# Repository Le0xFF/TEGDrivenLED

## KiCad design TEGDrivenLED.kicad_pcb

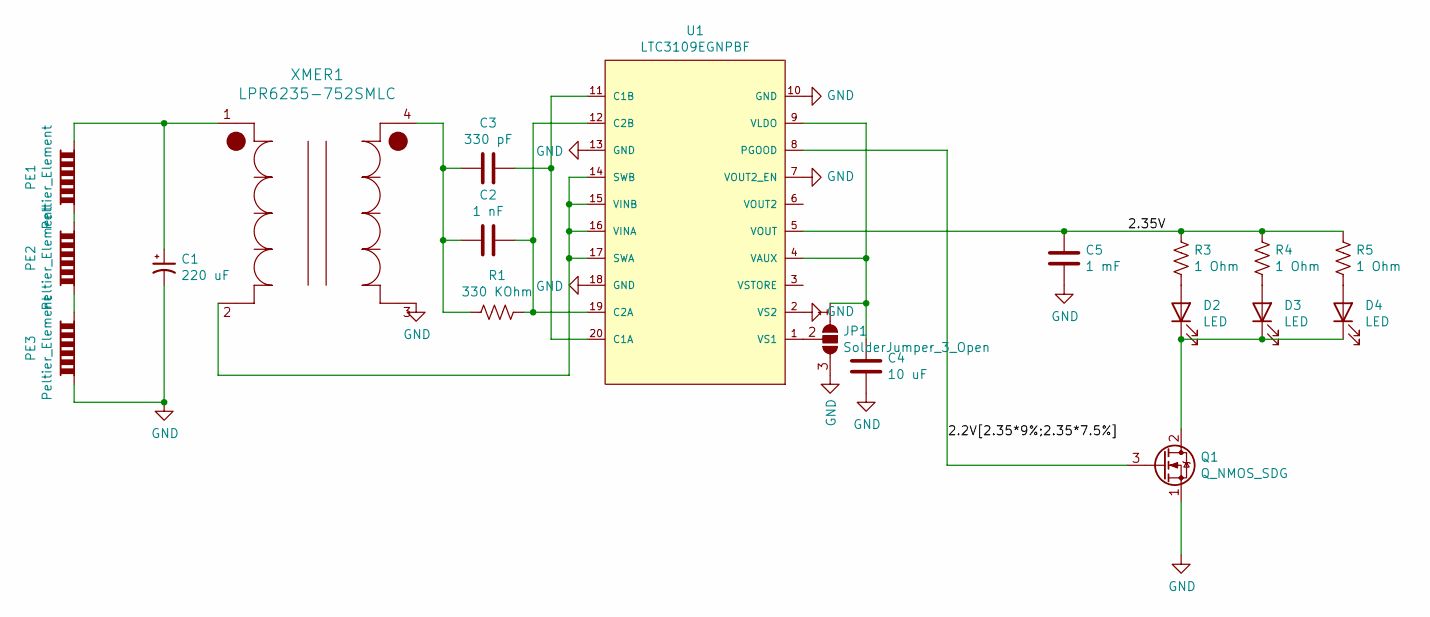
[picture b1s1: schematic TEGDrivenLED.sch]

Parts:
C1: 220 uF; C_1206_3216Metric_Pad1.33x1.80mm_HandSolder
C2: 1 nF; C_0805_2012Metric_Pad1.18x1.45mm_HandSolder
C3: 330 pF; C_0805_2012Metric_Pad1.18x1.45mm_HandSolder
C4: 10 uF; C_0805_2012Metric_Pad1.18x1.45mm_HandSolder
C5: 1 mF; CP_EIA-7132-28_AVX-C_Pad2.72x3.50mm_HandSolder
D2, D3, D4: LED; LED_1206_3216Metric_Pad1.42x1.75mm_HandSolder
JP1: SolderJumper_3_Open; SolderJumper-3_P1.3mm_Open_RoundedPad1.0x1.5mm_NumberLabels
PE1, PE2, PE3: Peltier_Element; CM23-1.9-01AC
Q1: Q_NMOS_SDG; SOT-23
R1: 330 KOhm; R_0805_2012Metric_Pad1.20x1.40mm_HandSolder
R3, R4, R5: 1 Ohm; R_0805_2012Metric_Pad1.20x1.40mm_HandSolder
U1: LTC3109EGNPBF; Linear_Technology-LTC3109EGNPBF-Level_A
XMER1: LPR6235-752SMLC

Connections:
/2.2V[2.35*9%;2.35*7.5%]: Q1.3 (G), U1.8 (PGOOD)
/2.35V: C5.1, R3.1, R4.1, R5.1, U1.5 (VOUT)
GND: C1.2, C4.2, C5.2, JP1.3 (B), PE3.1, Q1.1 (S), U1.2 (VS2), U1.7 (VOUT2_EN), U1.10 (GND), U1.13 (GND), U1.18 (GND), XMER1.3
unnamed: C1.1, PE1.2, XMER1.1
unnamed: C2.1, R1.1, U1.12 (C2B), U1.19 (C2A)
unnamed: C2.2, C3.2, R1.2, XMER1.4
unnamed: C3.1, U1.11 (C1B), U1.20 (C1A)
unnamed: C4.1, JP1.1 (A), U1.4 (VAUX), U1.9 (VLDO)
unnamed: D2.1 (K), D3.1 (K), D4.1 (K), Q1.2 (D)
unnamed: D2.2 (A), R3.2
unnamed: D3.2 (A), R4.2
unnamed: D4.2 (A), R5.2
unnamed: JP1.2 (C), U1.1 (VS1)
unnamed: PE1.1, PE2.2
unnamed: PE2.1, PE3.2
unnamed: U1.14 (SWB), U1.15 (VINB), U1.16 (VINA), U1.17 (SWA), XMER1.2

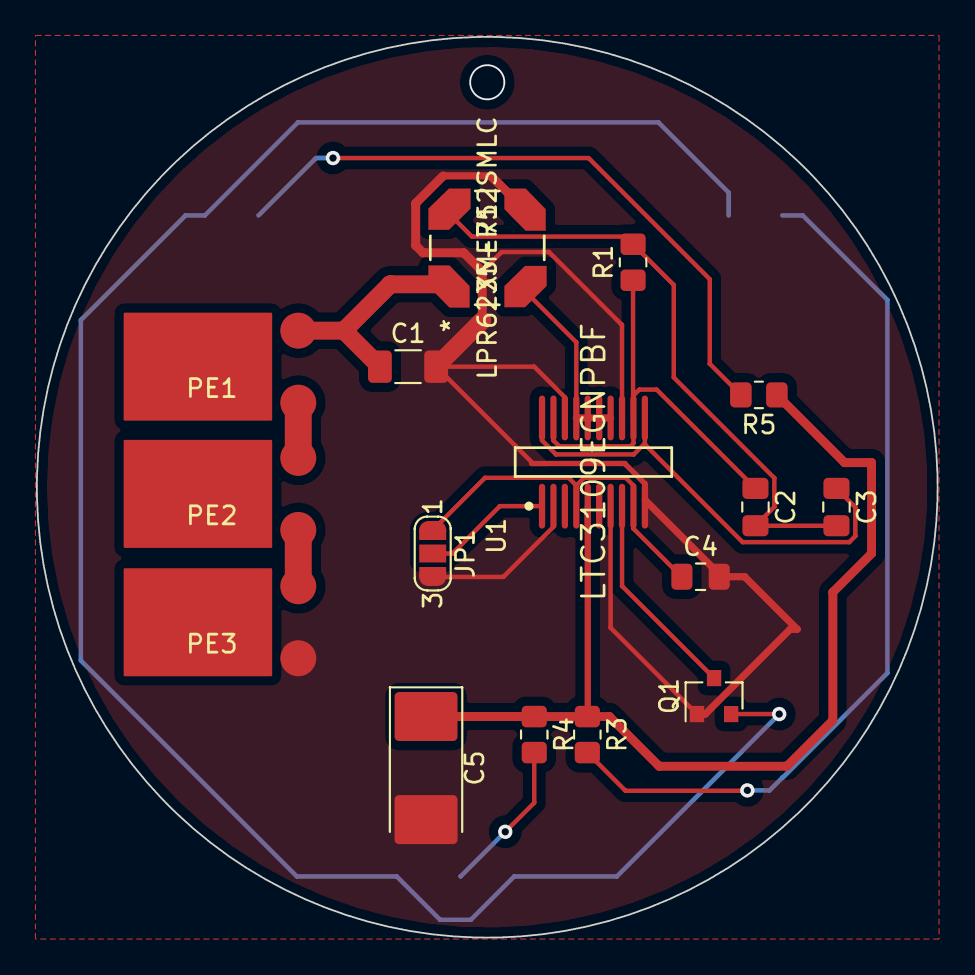
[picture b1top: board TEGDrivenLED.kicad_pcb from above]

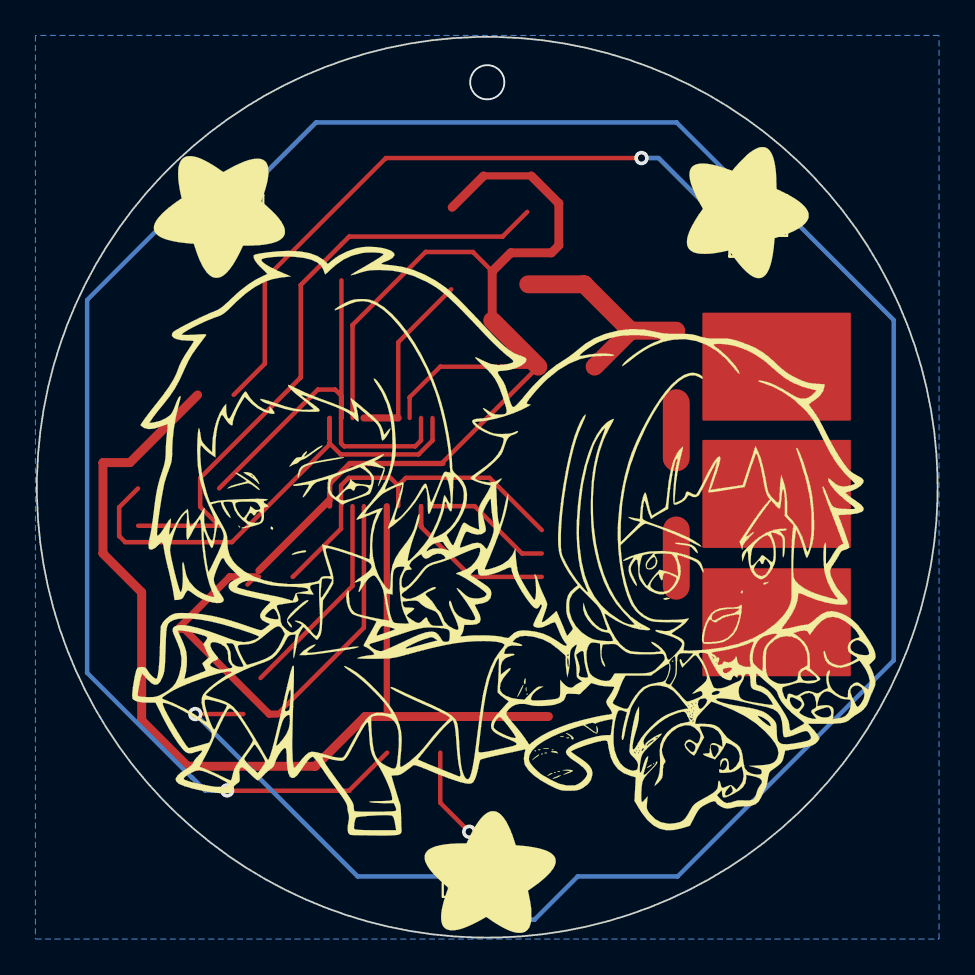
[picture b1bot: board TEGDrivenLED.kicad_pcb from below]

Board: 2 copper layers, 50.0 x 50.0 mm, 19 parts (3 on the bottom side), 16 nets.

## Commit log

2021-03-03 Files upload

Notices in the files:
parts and their libraries:
Copyright 2016 Accelerated Designs. All rights reserved.
